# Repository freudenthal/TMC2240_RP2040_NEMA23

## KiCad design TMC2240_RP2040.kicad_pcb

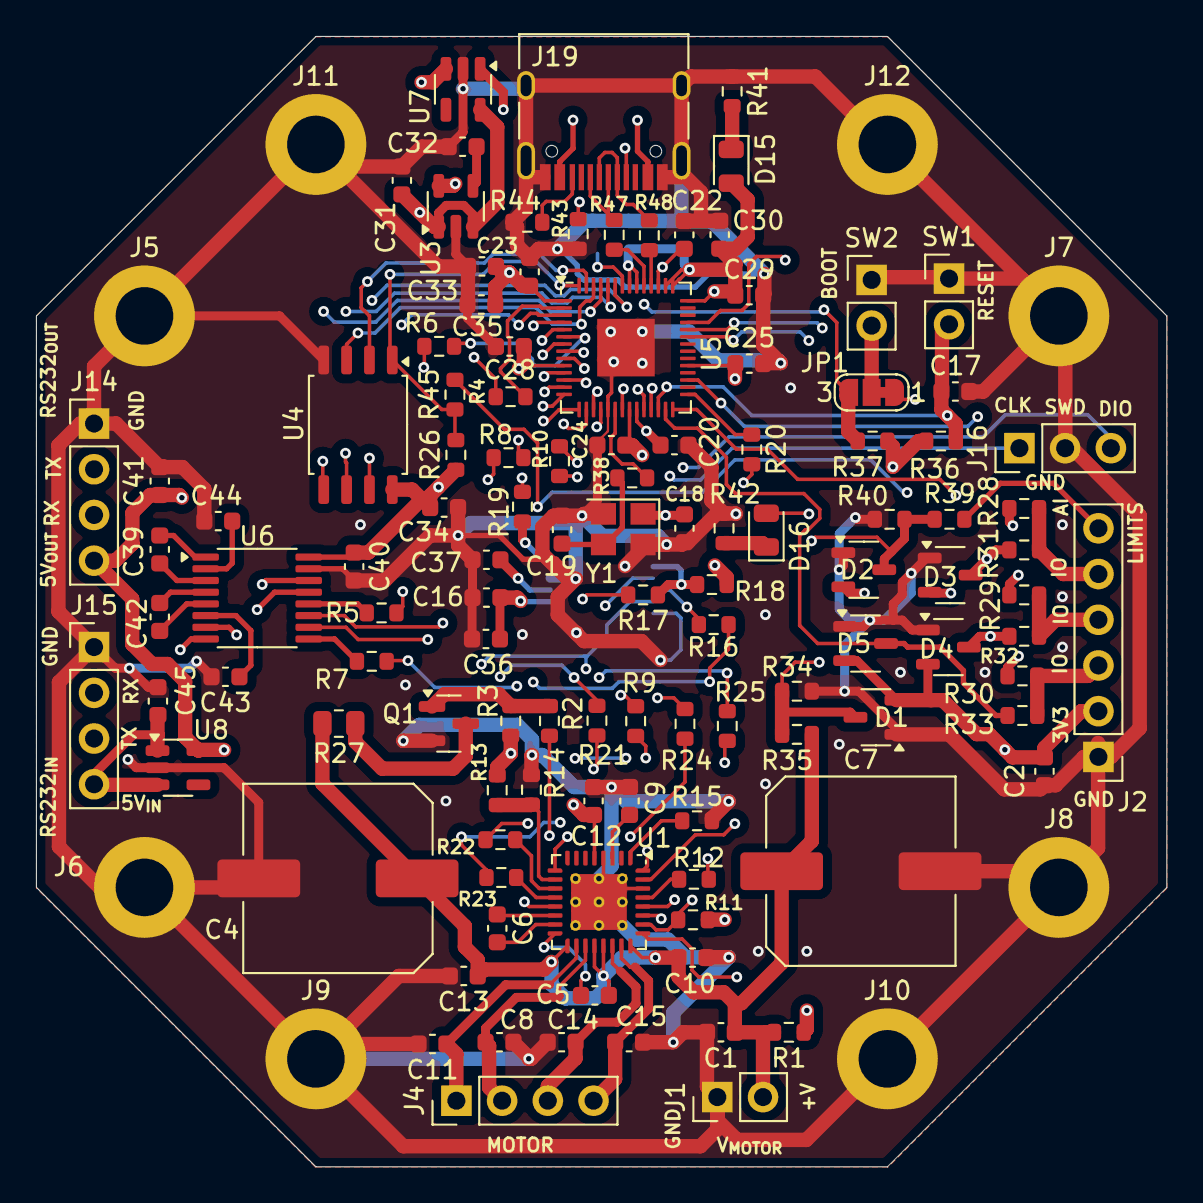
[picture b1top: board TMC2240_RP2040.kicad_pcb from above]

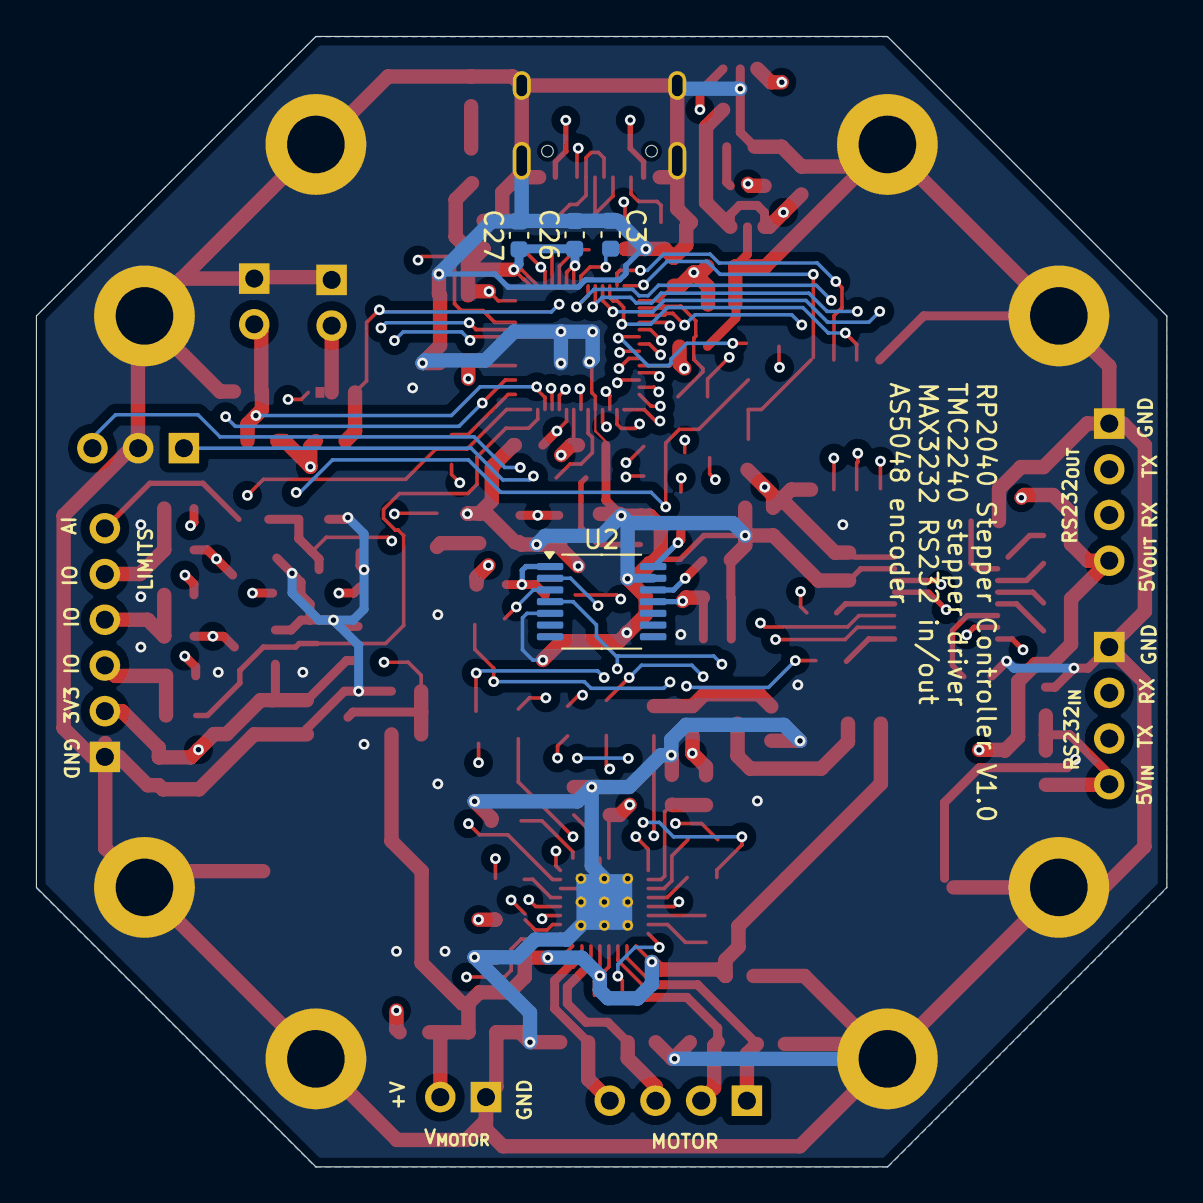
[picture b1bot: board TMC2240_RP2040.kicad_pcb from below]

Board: 4 copper layers, 62.8 x 62.8 mm, 125 parts (4 on the bottom side), 98 nets.

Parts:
C1, C2, C5, C10, C13, C39, C40, C41, C42, C43, C44, C45: 1uF; C_0603_1608Metric
C3, C20, C24, C25, C26, C27, C28, C29, C30, C34: 100n; C_0603_1608Metric
C4, C7: 100uF; C_Elec_10x10.2
C6: 22nF 50V; C_0603_1608Metric
C8, C11, C14, C15, C32: 470pF; C_0603_1608Metric
C9: 10uF; C_0603_1608Metric
C12, C16, C36, C37: 0.1uF; C_0603_1608Metric
C17, C22, C23: 1u; C_0603_1608Metric
C18, C19: 30pF; C_0603_1608Metric
C31, C35: 10u; C_0603_1608Metric
C33: 2.2uF; C_0603_1608Metric
D1, D2, D3, D4, D5: 0.1A; SOT-23-3
D15: POW_LED; LED_0805_2012Metric
D16: DBG_LED; LED_0805_2012Metric
J1: V_{MOTOR}; PinHeader_1x02_P2.54mm_Vertical
J2: LIMIT; PinHeader_1x06_P2.54mm_Vertical
J4: Motor; PinHeader_1x04_P2.54mm_Vertical
J5, J6, J7, J8, J9, J10, J11, J12: Screw_Terminal_01x01; MountingHole_3.2mm_M3_DIN965_Pad
J14: RSS232Out; PinHeader_1x04_P2.54mm_Vertical
J15: RSS232In; PinHeader_1x04_P2.54mm_Vertical
J16: SWD; PinHeader_1x03_P2.54mm_Vertical
J19: USB_C_Receptacle_USB2.0; USB_C_Receptacle_HRO_TYPE-C-31-M-12
JP1: UBUT_SEL; SolderJumper-3_P1.3mm_Bridged12_RoundedPad1.0x1.5mm_NumberL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
Q1: Q_NMOS_GSD; SOT-23
R1, R13: NSΩ; R_0603_1608Metric
R2: 10Ω; R_0603_1608Metric
R3, R11, R18: 10kΩ; R_0603_1608Metric
R4, R5, R6, R7, R8, R9, R10, R12, R16, R17, R19, R20, R21, R22, R23, R24, R25, R28, R29, R30, R31, R32, R33, R39, R40: 100Ω; R_0603_1608Metric
R14, R15, R34: 1kΩ; R_0603_1608Metric
R26: 10k; R_0603_1608Metric
R27: 10Ω; R_0805_2012Metric
R35: 30kΩ; R_0603_1608Metric
R36: 10K; R_0603_1608Metric
R37, R43, R44: 5.1K; R_0603_1608Metric
R38, R45: 1k; R_0603_1608Metric
R41, R42: 470R; R_0603_1608Metric
R47, R48: 27R; R_0603_1608Metric
SW1: Reset; PinHeader_1x02_P2.54mm_Vertical
SW2: UBUT; PinHeader_1x02_P2.54mm_Vertical
U1: TMC2240_TQFN; TQFN-32-1EP_5x5mm_P0.5mm_EP3.1x3.1mm_ThermalVias
U2: AS5048A; TSSOP-14_4.4x5mm_P0.65mm
U3: MIC5219-3.3YM5; SOT-23-5
U4: W25Q128JVS; SOIC-8_5.23x5.23mm_P1.27mm
U5: RP2040; QFN-56-1EP_7x7mm_P0.4mm_EP3.2x3.2mm
U6: MAX3232; TSSOP-16_4.4x5mm_P0.65mm
U7, U8: MAX40200AUK; SOT-23-5
Y1: YIC-12M20P2/XT324-10/10; Crystal_SMD_3225-4Pin_3.2x2.5mm

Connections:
+1V1: C3.1, C20.1, C22.1, U5.23 (DVDD), U5.45 (VREG_VOUT), U5.50 (DVDD)
+3.3V: C2.1, C12.1, C16.1, C23.1, C24.1, C25.1, C26.1, C27.1, C28.1, C29.1, C30.1, C33.1, C34.1, C35.1, C36.1, C40.1, D1.2 (K), D2.2 (K), D3.2 (K), D4.2 (K), D5.2 (K), D15.2 (A), J2.2, R3.2, R11.1, R13.1, R18.1, R26.1, R28.2, R29.2, R30.2, R36.1, R37.2, U1.5 (V_{IO}), U2.11 (VDD5V), U3.5 (OUT), U4.8 (VCC), U5.1 (IOVDD), U5.10 (IOVDD), U5.22 (IOVDD), U5.33 (IOVDD), U5.42 (IOVDD), U5.43 (ADC_AVDD), U5.44 (VREG_IN), U5.48 (USB_VDD), U5.49 (IOVDD), U6.16 (VCC)
+5V: C31.1, C41.1, J14.4, R1.1, U3.1 (IN), U3.3 (EN), U7.5 (OUT), U8.5 (OUT)
/AS5048AEncoder/CLK: R10.1, U1.27 (SCLK), U2.2 (CLK)
/AS5048AEncoder/MISO: R16.1, U2.3 (MISO)
/AS5048AEncoder/MOSI: R8.1, U1.28 (SDI), U2.4 (MOSI)
/AS5048AEncoder/PWM: R19.1, U2.14 (PWM)
/AS5048AEncoder/~CS: R17.1, R18.2, U2.1 (~CSn)
/AccessoryConnections/ADC: D2.3 (A), R39.1, R40.1, U5.39 (GPIO27_ADC1)
/AccessoryConnections/LIMITH: D5.3 (A), R33.2, U5.27 (GPIO16)
/AccessoryConnections/LIMITL: D3.3 (A), R31.2, U5.31 (GPIO20)
/AccessoryConnections/LIMITM: D4.3 (A), R32.2, U5.28 (GPIO17)
/DualRS232UART/RX1: R5.1, U6.12 (R1OUT)
/DualRS232UART/RX2: R7.1, U6.9 (R2OUT)
/DualRS232UART/TX1: R4.1, U6.11 (T1IN)
/DualRS232UART/TX2: R6.1, U6.10 (T2IN)
/RP2040uC/ADC0_GP26: D1.3 (A), R34.1, R35.1, U5.38 (GPIO26_ADC0)
/RP2040uC/GPIO2: JP1.3 (B), R37.1, U5.4 (GPIO2)
/RP2040uC/GPIO25: D16.2 (A), U5.37 (GPIO25)
/RP2040uC/QSPI_SCLK: U4.6 (CLK), U5.52 (QSPI_SCLK)
/RP2040uC/QSPI_SD0: U4.5 (DI(IO0)), U5.53 (QSPI_SD0)
/RP2040uC/QSPI_SD1: U4.2 (DO(IO1)), U5.55 (QSPI_SD1)
/RP2040uC/QSPI_SD2: U4.3 (IO2), U5.54 (QSPI_SD2)
/RP2040uC/QSPI_SD3: U4.7 (IO3), U5.51 (QSPI_SD3)
/RP2040uC/QSPI_SS: R26.2, R45.1, U4.1 (~CS), U5.56 (QSPI_SS)
/RP2040uC/RUN: C17.1, R36.2, SW1.2, U5.26 (RUN)
/RP2040uC/RX0_SCL0_SPIS0_GP1: R5.2, U5.3 (GPIO1)
/RP2040uC/RX0_SCL0_SPIS1_GP13: R23.2, U5.16 (GPIO13)
/RP2040uC/RX1_SCL0_SPIS0_GP5: R7.2, U5.7 (GPIO5)
/RP2040uC/RX1_SCL0_SPIS1_GP9: R9.2, U5.12 (GPIO9)
/RP2040uC/SCL1_SPII0_GP3: R21.2, U5.5 (GPIO3)
/RP2040uC/SCL1_SPII0_GP7: R17.2, U5.9 (GPIO7)
/RP2040uC/SCL1_SPII1_GP11: R12.2, R16.2, U5.14 (GPIO11)
/RP2040uC/SCL1_SPII1_GP15: R25.2, U5.18 (GPIO15)
/RP2040uC/SDA1_SPIC0_GP6: R19.2, U5.8 (GPIO6)
/RP2040uC/SDA1_SPIC0_GP18: R20.2, U5.29 (GPIO18)
/RP2040uC/SDA1_SPIC1_GP10: R10.2, U5.13 (GPIO10)
/RP2040uC/SDA1_SPIC1_GP14: R24.2, U5.17 (GPIO14)
/RP2040uC/SWCLK: J16.1, U5.24 (SWCLK)
/RP2040uC/SWDIO: J16.3, U5.25 (SWD)
/RP2040uC/TX0_SDA0_SPIO0_GP0: R4.2, U5.2 (GPIO0)
/RP2040uC/TX0_SDA0_SPIO1_GP12: R22.2, U5.15 (GPIO12)
/RP2040uC/TX1_SDA0_SPIO0_GP4: R6.2, U5.6 (GPIO4)
/RP2040uC/TX1_SDA0_SPIO1_GP8: R8.2, U5.11 (GPIO8)
/RP2040uC/USB_D+: J19.A6 (D+), J19.B6 (D+), R47.1
/RP2040uC/USB_D-: J19.A7 (D-), J19.B7 (D-), R48.1
/RP2040uC/XIN: C18.1, U5.21 (XOUT), Y1.1
/RP2040uC/XOUT: R38.1, U5.20 (XIN)
/RP2040uC/~USB_BOOT: JP1.1 (A), R45.2
/StepperTMC2240/DIAG0: R22.1, U1.11 (DIAG0)
/StepperTMC2240/DIAG1: R23.1, U1.12 (DIAG1)
/StepperTMC2240/DIR: R21.1, U1.32 (DIR)
/StepperTMC2240/OV: R2.1, U1.13 (OV)
/StepperTMC2240/SDO: R12.1, U1.29 (SDO)
/StepperTMC2240/STEP: R20.1, U1.31 (STEP)
/StepperTMC2240/~CS: R9.1, R11.2, U1.26 (~CS)
/StepperTMC2240/~DRV_EN: R24.1, U1.9 (~DRV_EN)
/StepperTMC2240/~SLEEP: R25.1, U1.25 (~SLEEP)
GND: C1.2, C2.2, C3.2, C4.2, C7.2, C8.2, C9.2, C10.2, C11.2, C12.2, C13.2, C14.2, C15.2, C16.2, C17.2, C18.2, C19.2, C20.2, C22.2, C23.2, C24.2, C25.2, C26.2, C27.2, C28.2, C29.2, C30.2, C31.2, C32.2, C33.2, C34.2, C35.2, C36.2, C37.2, C40.2, C41.2, C43.2, C44.2, C45.2, D1.1 (K), D2.1 (K), D3.1 (K), D4.1 (K), D5.1 (K), J1.1, J2.1, J5.1, J6.1, J7.1, J8.1, J9.1, J10.1, J11.1, J12.1, J14.1, J15.1, J16.2, J19.A1 (GND), J19.A12 (GND), J19.B1 (GND), J19.B12 (GND), J19.S1 (SHIELD), Q1.2 (S), R14.1, R15.1, R34.2, R40.2, R41.1, R42.1, R43.2, R44.2, SW1.1, SW2.1, U1.4 (AGND), U1.30 (CLK), U1.33 (GND), U2.5 (TEST), U2.13 (GND), U3.2 (GND), U4.4 (GND), U5.19 (TESTEN), U5.57 (GND), U6.15 (GND), U7.2 (GND), U8.2 (GND), Y1.2, Y1.4
unnamed: C19.1, R38.2, Y1.3
unnamed: D15.1 (K), R41.2
unnamed: D16.1 (K), R42.2
unnamed: J2.3, R30.1, R33.1
unnamed: J2.4, R29.1, R32.1
unnamed: J2.5, R28.1, R31.1
unnamed: J2.6, R39.2
unnamed: C11.1, J4.1, U1.18 (OUT1B)
unnamed: C8.1, J4.2, U1.19 (OUT2B)
unnamed: C14.1, J4.3, U1.22 (OUT2A)
unnamed: C15.1, J4.4, U1.23 (OUT1A)
unnamed: J14.2, U6.7 (T2OUT)
unnamed: J14.3, U6.8 (R2IN)
unnamed: J15.2, U6.13 (R1IN)
unnamed: J15.3, U6.14 (T1OUT)
unnamed: C45.1, J15.4, U8.1 (VDD), U8.3 (EN)
unnamed: J19.A5 (CC1), R43.1
unnamed: J19.B5 (CC2), R44.1
unnamed: JP1.2 (C), SW2.2
unnamed: Q1.3 (D), R27.1
unnamed: Q1.1 (G), R2.2, R3.1
unnamed: C6.1, U1.14 (CPI)
unnamed: C6.2, U1.15 (CPO)
unnamed: R15.2, U1.1 (IREF)
unnamed: R13.2, R14.2, U1.10 (UARTEN)
unnamed: C9.1, U1.3 (V_{1V8})
unnamed: C5.1, U1.16 (V_{CP})
unnamed: C37.1, U2.12 (VDD3V)
unnamed: C32.1, U3.4 (BP)
unnamed: R48.2, U5.46 (USB_DM)
unnamed: R47.2, U5.47 (USB_DP)
unnamed: C39.1, U6.1 (C1+)
unnamed: C39.2, U6.3 (C1-)
unnamed: C42.1, U6.4 (C2+)
unnamed: C42.2, U6.5 (C2-)
unnamed: C44.1, U6.2 (VS+)
unnamed: C43.1, U6.6 (VS-)
VBUS: J19.A4 (VBUS), J19.A9 (VBUS), J19.B4 (VBUS), J19.B9 (VBUS), U7.1 (VDD), U7.3 (EN)
VCC: C1.1, C4.1, C5.2, C7.1, C10.1, C13.1, J1.2, R1.2, R27.2, R35.2, U1.17 (V_{S}), U1.20 (V_{S}), U1.21 (V_{S}), U1.24 (V_{S})

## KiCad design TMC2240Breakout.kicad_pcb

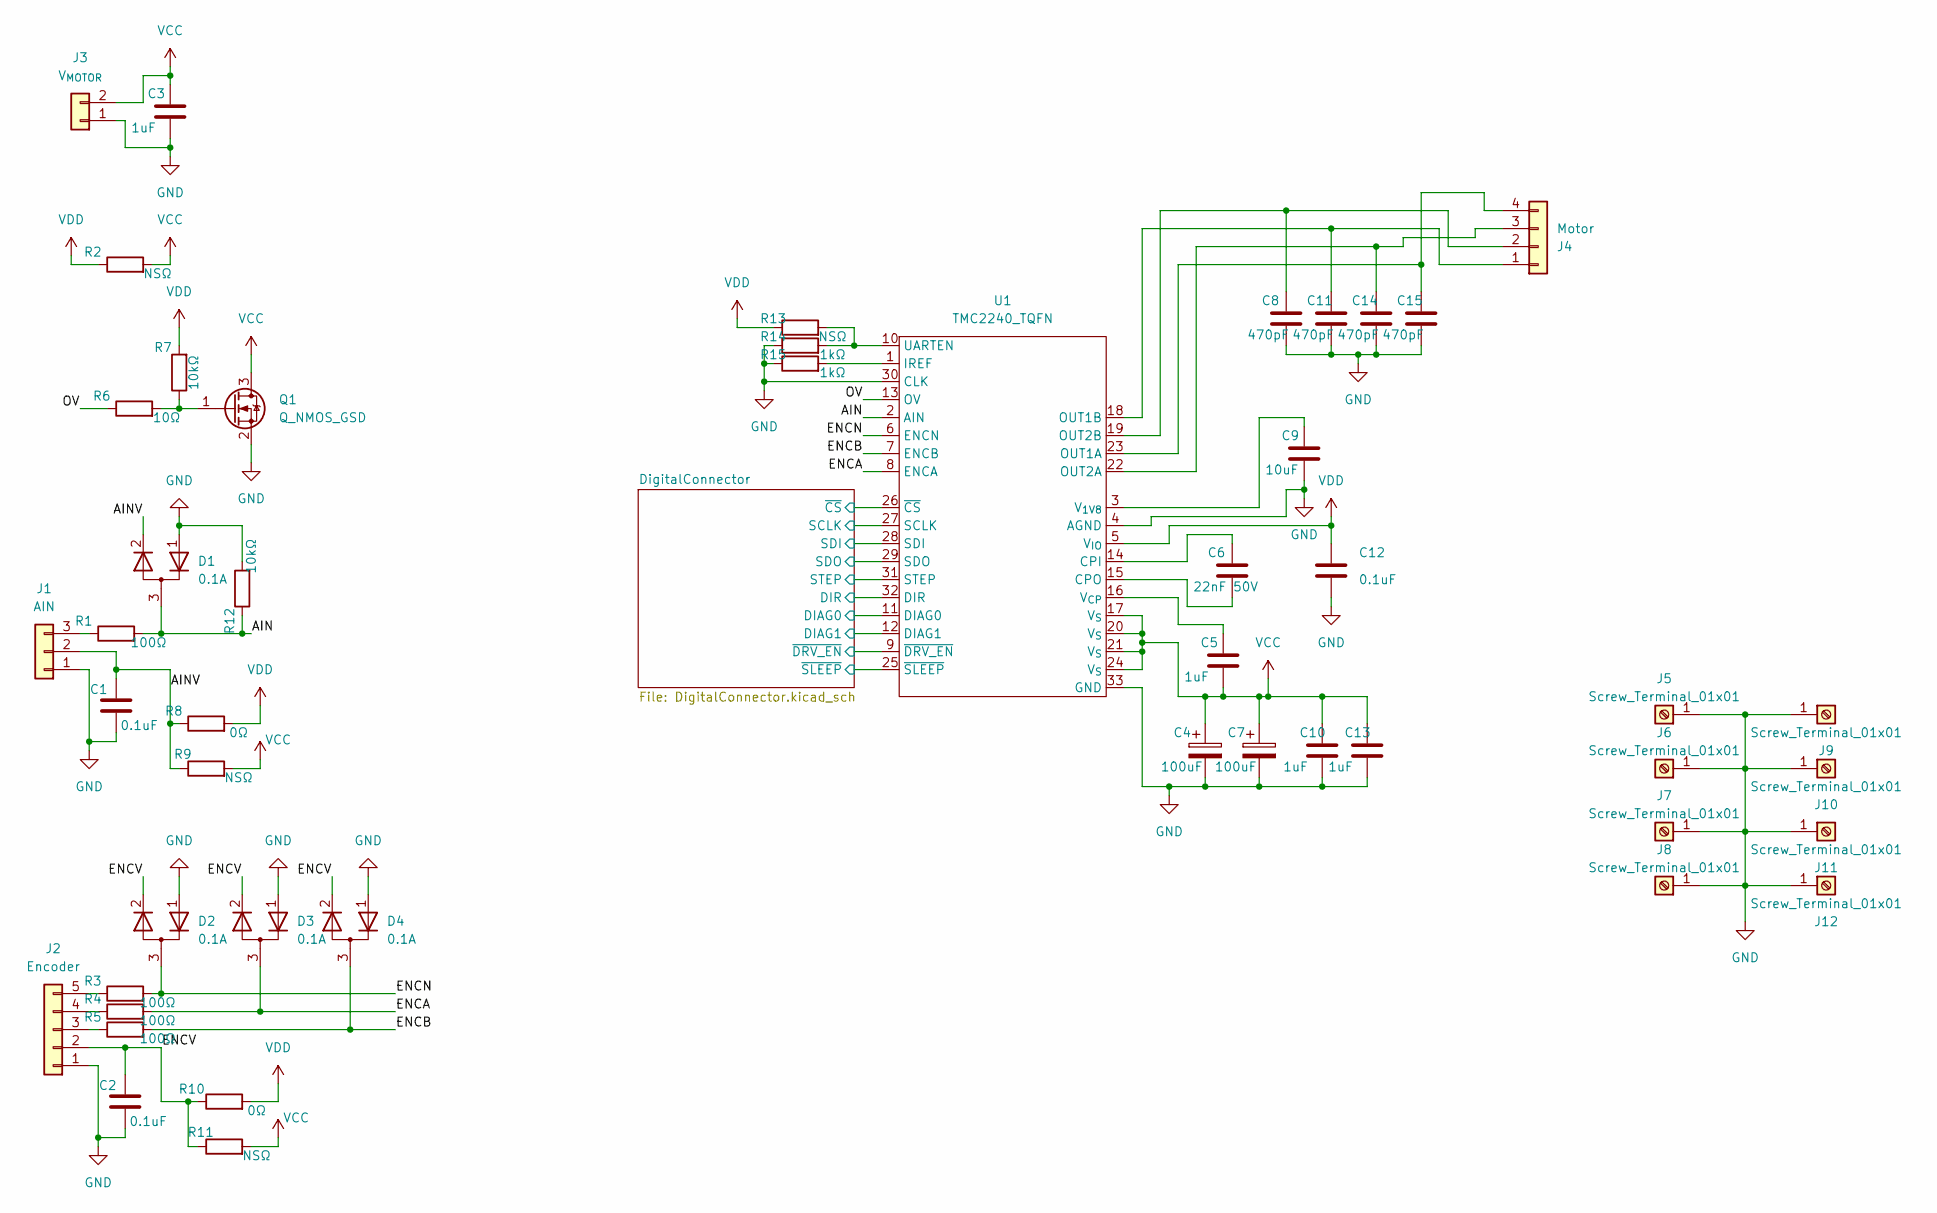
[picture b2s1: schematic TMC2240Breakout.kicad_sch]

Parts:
C1, C2, C12: 0.1uF; C_0805_2012Metric
C3, C5, C10, C13: 1uF; C_0805_2012Metric
C4, C7: 100uF; C_Elec_10x10.2
C6: 22nF 50V; C_0805_2012Metric
C8, C11, C14, C15: 470pF; C_0805_2012Metric
C9: 10uF; C_0805_2012Metric
D1, D2, D3, D4: 0.1A; SOT-23-3
J1: AIN; PinHeader_1x03_P2.54mm_Vertical
J2: Encoder; PinHeader_1x05_P2.54mm_Vertical
J3: V_{MOTOR}; TerminalBlock_Phoenix_MKDS-1,5-2-5.08_1x02_P5.08mm_Horizont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
J4: Motor; TerminalBlock_Phoenix_MKDS-1,5-4-5.08_1x04_P5.08mm_Horizont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
J5, J6, J7, J8, J9, J10, J11, J12: Screw_Terminal_01x01; MountingHole_3.2mm_M3_DIN965_Pad
Q1: Q_NMOS_GSD; SOT-23
R1, R3, R4, R5: 100Ω; R_0805_2012Metric
R2, R9, R11, R13: NSΩ; R_0805_2012Metric
R6: 10Ω; R_0805_2012Metric
R7, R12: 10kΩ; R_0805_2012Metric
R8, R10: 0Ω; R_0805_2012Metric
R14, R15: 1kΩ; R_0805_2012Metric
U1: TMC2240_TQFN; TQFN-32-1EP_5x5mm_P0.5mm_EP3.1x3.1mm_ThermalVias

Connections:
/AIN: D1.3 (A), R1.2, R12.1, U1.2 (AIN)
/AINV: C1.1, D1.2 (K), J1.2, R8.1, R9.1
/DigitalConnector/DIAG0: U1.11 (DIAG0); also elsewhere on the board
/DigitalConnector/DIAG1: U1.12 (DIAG1); also elsewhere on the board
/DigitalConnector/DIR: U1.32 (DIR); also elsewhere on the board
/DigitalConnector/SCLK: U1.27 (SCLK); also elsewhere on the board
/DigitalConnector/SDI: U1.28 (SDI); also elsewhere on the board
/DigitalConnector/SDO: U1.29 (SDO); also elsewhere on the board
/DigitalConnector/STEP: U1.31 (STEP); also elsewhere on the board
/DigitalConnector/~CS: U1.26 (~CS); also elsewhere on the board
/DigitalConnector/~DRV_EN: U1.9 (~DRV_EN); also elsewhere on the board
/DigitalConnector/~SLEEP: U1.25 (~SLEEP); also elsewhere on the board
/ENCA: D3.3 (A), R4.2, U1.8 (ENCA)
/ENCB: D4.3 (A), R5.2, U1.7 (ENCB)
/ENCN: D2.3 (A), R3.2, U1.6 (ENCN)
/ENCV: C2.1, D2.2 (K), D3.2 (K), D4.2 (K), J2.2, R10.1, R11.1
/OV: R6.1, U1.13 (OV)
GND: C1.2, C2.2, C3.2, C4.2, C7.2, C8.2, C9.2, C10.2, C11.2, C12.2, C13.2, C14.2, C15.2, D1.1 (K), D2.1 (K), D3.1 (K), D4.1 (K), J1.1, J2.1, J3.1, J5.1, J6.1, J7.1, J8.1, J9.1, J10.1, J11.1, J12.1, Q1.2 (S), R12.2, R14.1, R15.1, U1.4 (AGND), U1.30 (CLK), U1.33 (GND); also elsewhere on the board
unnamed: J1.3, R1.1
unnamed: J2.3, R5.1
unnamed: J2.4, R4.1
unnamed: J2.5, R3.1
unnamed: C11.1, J4.1, U1.18 (OUT1B)
unnamed: C8.1, J4.2, U1.19 (OUT2B)
unnamed: C14.1, J4.3, U1.22 (OUT2A)
unnamed: C15.1, J4.4, U1.23 (OUT1A)
unnamed: Q1.1 (G), R6.2, R7.1
unnamed: C6.1, U1.14 (CPI)
unnamed: C6.2, U1.15 (CPO)
unnamed: R15.2, U1.1 (IREF)
unnamed: R13.2, R14.2, U1.10 (UARTEN)
unnamed: C9.1, U1.3 (V_{1V8})
unnamed: C5.1, U1.16 (V_{CP})
VCC: C3.1, C4.1, C5.2, C7.1, C10.1, C13.1, J3.2, Q1.3 (D), R2.2, R9.2, R11.2, U1.17 (V_{S}), U1.20 (V_{S}), U1.21 (V_{S}), U1.24 (V_{S})
VDD: C12.1, R2.1, R7.2, R8.2, R10.2, R13.1, U1.5 (V_{IO}); also elsewhere on the board

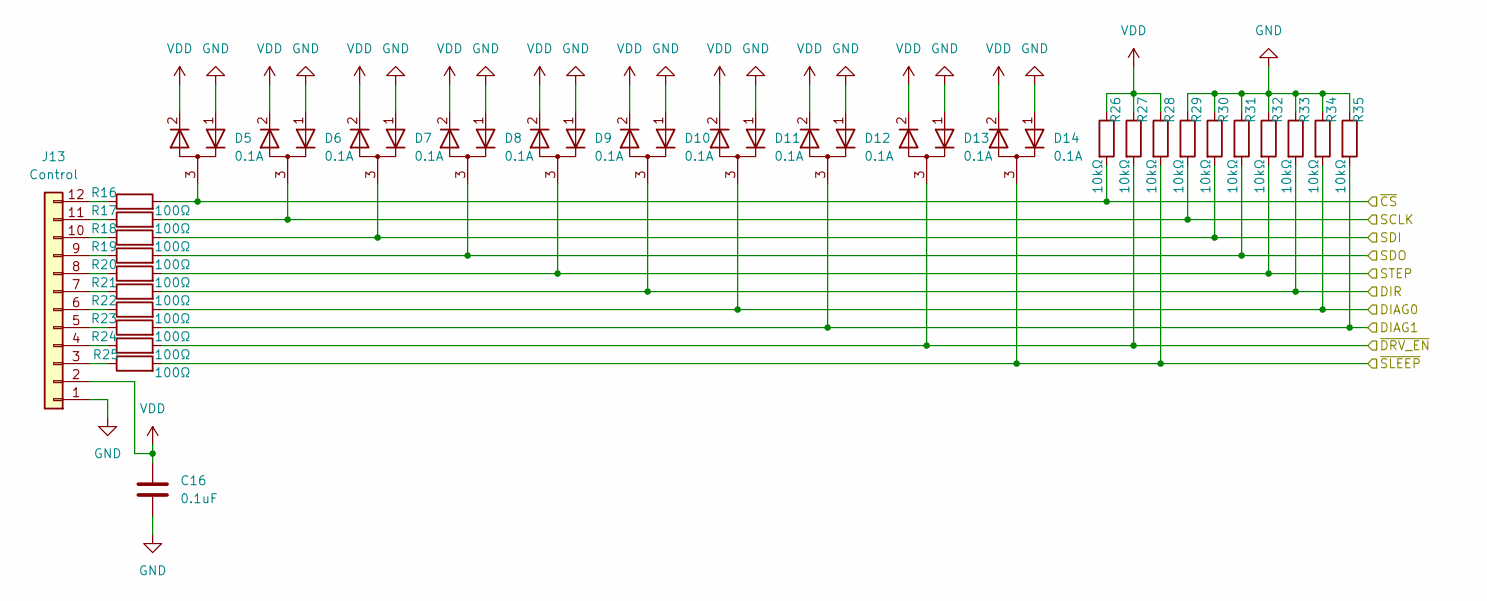
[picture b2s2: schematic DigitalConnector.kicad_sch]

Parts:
C16: 0.1uF; C_0805_2012Metric
D5, D6, D7, D8, D9, D10, D11, D12, D13, D14: 0.1A; SOT-23-3
J13: Control; PinHeader_2x06_P2.54mm_Vertical
R16, R17, R18, R19, R20, R21, R22, R23, R24, R25: 100Ω; R_0805_2012Metric
R26, R27, R28, R29, R30, R31, R32, R33, R34, R35: 10kΩ; R_0805_2012Metric

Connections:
/DigitalConnector/DIAG0: D11.3 (A), R22.2, R34.2; also elsewhere on the board
/DigitalConnector/DIAG1: D12.3 (A), R23.2, R35.2; also elsewhere on the board
/DigitalConnector/DIR: D10.3 (A), R21.2, R33.2; also elsewhere on the board
/DigitalConnector/SCLK: D6.3 (A), R17.2, R29.2; also elsewhere on the board
/DigitalConnector/SDI: D7.3 (A), R18.2, R30.2; also elsewhere on the board
/DigitalConnector/SDO: D8.3 (A), R19.2, R31.2; also elsewhere on the board
/DigitalConnector/STEP: D9.3 (A), R20.2, R32.2; also elsewhere on the board
/DigitalConnector/~CS: D5.3 (A), R16.2, R26.2; also elsewhere on the board
/DigitalConnector/~DRV_EN: D13.3 (A), R24.2, R27.2; also elsewhere on the board
/DigitalConnector/~SLEEP: D14.3 (A), R25.2, R28.2; also elsewhere on the board
GND: C16.2, D5.1 (K), D6.1 (K), D7.1 (K), D8.1 (K), D9.1 (K), D10.1 (K), D11.1 (K), D12.1 (K), D13.1 (K), D14.1 (K), J13.1, R29.1, R30.1, R31.1, R32.1, R33.1, R34.1, R35.1; also elsewhere on the board
unnamed: J13.3, R25.1
unnamed: J13.4, R24.1
unnamed: J13.5, R23.1
unnamed: J13.6, R22.1
unnamed: J13.7, R21.1
unnamed: J13.8, R20.1
unnamed: J13.9, R19.1
unnamed: J13.10, R18.1
unnamed: J13.11, R17.1
unnamed: J13.12, R16.1
VDD: C16.1, D5.2 (K), D6.2 (K), D7.2 (K), D8.2 (K), D9.2 (K), D10.2 (K), D11.2 (K), D12.2 (K), D13.2 (K), D14.2 (K), J13.2, R26.1, R27.1, R28.1; also elsewhere on the board

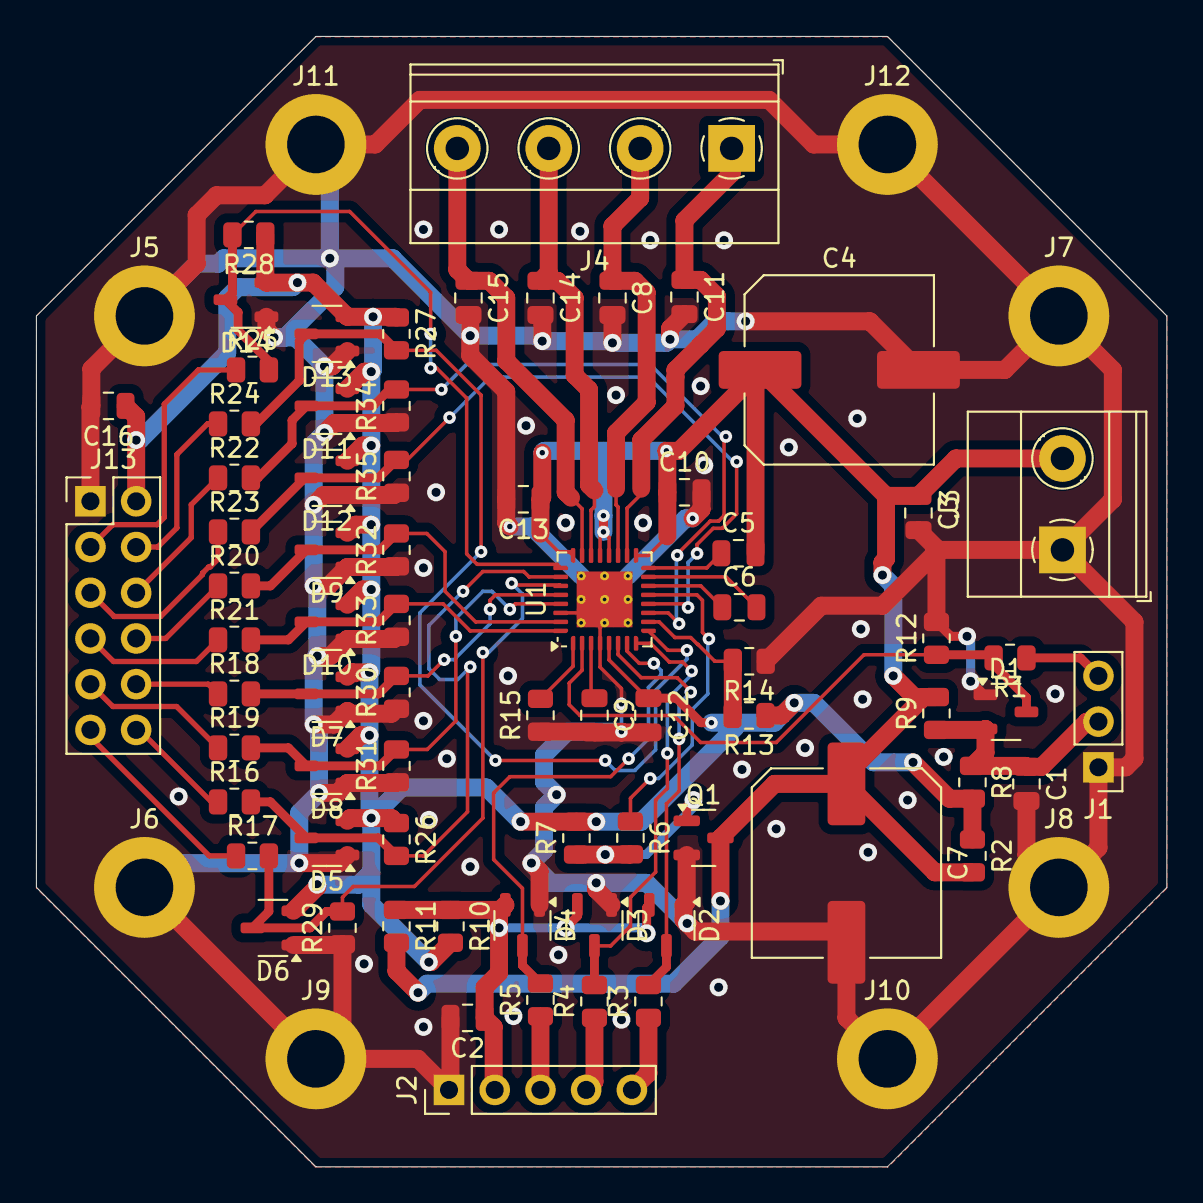
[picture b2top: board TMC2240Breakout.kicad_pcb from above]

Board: 2 copper layers, 62.8 x 62.8 mm, 80 parts (0 on the bottom side), 45 nets.

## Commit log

2024-04-10 Added RP2040.
2024-04-11 Added an ADC input pin, and protection diodes. Updated the OV load resistor to 0805. Cleaned up a few silk screen overlaps.
2024-04-11 Added more silk screen labels and generated manufacturing files.
